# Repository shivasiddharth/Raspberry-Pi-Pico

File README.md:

# Raspberry-Pi-Pico
 Aggregate of Raspberry Pi Pico related codes, firmware, libraries, etc.      

*************************************
## Getting started with Micropython    
*************************************   

### Setting the firmware    
1. Download the MicroPython firmware from the **Firmware** directory in the **Micropython** folder or from official Raspberry Pi's site by clicking [here](https://www.raspberrypi.org/documentation/pico/getting-started/static/5d8e777377e8dbe23cf36360d6efc727/pico_micropython_20210121.uf2).     
2. Push and hold the BOOTSEL button and plug your Pico into the USB port of your Raspberry Pi or other computer. Release the BOOTSEL button after your Pico is detected.     
3. It will mount as a Mass Storage Device called RPI-RP2.     
4. Place the MicroPython UF2 file onto the RPI-RP2 volume. The Raspberry Pi Pico should reboot and be ready for programming using Micropython.   

### Programming the Pico   
1. You can use any Micropython based IDE for programming the Pico. However, the recommended IDE is the Thonny.     
2. Raspberry Pi boards come with Thonny preinstalled. If you are using other systems, you can download and install Thonny from [here](https://thonny.org).    
3. To program the Pico, after opening the Thonny IDE, click on **Run** menu and click on the **Select interpreter** option. And from the Drop-down, select Raspberry Pi Pico.    

**************************************
## Getting started with Circuitpython     
**************************************    

### Setting the firmware
1. Download the MicroPython firmware from the **Firmware** directory in the **Circuitpython** folder or from official Adafruit's site by clicking [here](https://downloads.circuitpython.org/bin/raspberry_pi_pico/en_US/adafruit-circuitpython-raspberry_pi_pico-en_US-6.2.0-beta.0.uf2).     
2. Push and hold the BOOTSEL button and plug your Pico into the USB port of your Raspberry Pi or other computer. Release the BOOTSEL button after your Pico is detected.     
3. It will mount as a Mass Storage Device called RPI-RP2.     
4. Place the Circuitpython UF2 file onto the RPI-RP2 volume. The Raspberry Pi Pico should reboot and ready for programming using Micropython.   

### Programming the Pico   
1. You can use any Circuitpython based IDE for programming the Pico. However, the recommended IDE is the Mu.     
2. Raspberry Pi boards come with Thonny preinstalled. If you are using other systems, you can download and install Mu from [here](https://codewith.mu).    
3. To program the Pico, after opening the Mu IDE. Click on the Serial menu to automatically connect your Pico to the Mu IDE.   
4. Download the desired files from the **Libraries** folder and place it under the **lib** folder on the Pico or download the library zip file and extract it to the **lib** folder on the Pico.   

## Credits to      
1. Adafruit for the Circuitpython libraries and firmware.  
2. Raspberry Pi Foundation for the firmware.   
3. [Peter Hinch](https://github.com/peterhinch) for [micropython-async](https://github.com/peterhinch/micropython-async) and aswitch.py.         
4. [Mike Causer](https://github.com/mcauser) for EEPROM library [micropython-tinyrtc-i2c](https://github.com/mcauser/micropython-tinyrtc-i2c).

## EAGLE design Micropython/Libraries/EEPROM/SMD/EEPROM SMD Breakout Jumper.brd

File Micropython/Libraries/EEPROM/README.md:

## EEPROM Pinout and Connection    
    
The EEPROM has 8 pins, of which 3 are address pins as shown in the figure. The communication between the EEPROm and the microcontroller is via I2C. By setting the address pins A0, A1, A2 to either high or low, the default I2C address of the EEPROM chip can be configured. It is suggested to connect all the address pins to ground, unless you have multiple I2C devices or multiple EEPROMs connected.   

The WP or Write Protect pin when set to high prevents anything from being written on to the EEPROM. When the WP pin is connected to ground, write protection is disabled and things can be written on to the EEPROM.   

And then there is is the usual SDA (I2C Data), SCL (I2C Clock), Vcc (Supply) and Gnd (Ground) pins.    

The SDA, SCL and WP should not be left floating and hence they need to be pulled up via 3.9k resistors. The schematic for the EEPROM has also been attached. Please go through the same for clarity.   

## EEPROM PCB    
I have designed PCBs for making the Pi Pico-EEPROM connection easier. There are variants to the PCB designed. In the sample PCB image, you can see that one has a jumper for write protection and in the other, the write protection pin has been exposed.    

The advantage of using the board with the write protection pin exposed is that, the write protection can be software controlled, i.e., it can be enabled or disabled by setting the pin to Low or High.   

Other than the SMD versions, I have designed DIP versions as well. You can find the eagle files and gerber files here in the aobe folders.   

I got myself the SMD version of the board with the write protection pin exposed printed. I used the services of https://jlcpcb.com for printing as like all my projects. Feel free to modify the the board layout, schematics for your project and get them printed or make your own board using a general purpose PCB.   

## EEPROM-Pi Pico Connection    
My connection is as follows:    

EEPROM SDA --> Pi Pico GP0    

EEPROM SDA --> Pi Pico GP1    

EEPROM VCC --> Pi Pico 3V3 (OUT)    

EEPROM WP --> Pi Pico GND    

EEPROm GND --> Pi Pico GND    

The Raspberry Pi Pico has a number of I2C lines. Choose the ones comfortable to you.    

## Using the EEPROM in Your Program   
I have used Micropython to work with the EEPROM chip. I have modified the Micropython EERPOM libraries of [Mike Causer](https://github.com/mcauser).      

There are two parameters of the EEPROM to consider which are the bytes per page(bpp or BPP) and the pages. The total EEPROM memory is BPP x Number of Pages.    

For the same EEPROM capacity different manufactures may have different values of BPP and Number of Pages. Make sure to check them out and change those values in the library files.    

I have provided library files for two different versions just for reference and to show the difference. If you are using any other EEPROM version please do pay attention to the shown differences and change your library file accordingly.    

After making the desired changes to the library file, import it onto the Pi Pico. I have provided a demo script that exploits almost all the functions of the EEPROM. You cna find the demo script in the examples folder.   

I have gone through a lot of detail and have explained the demo script in this video below.

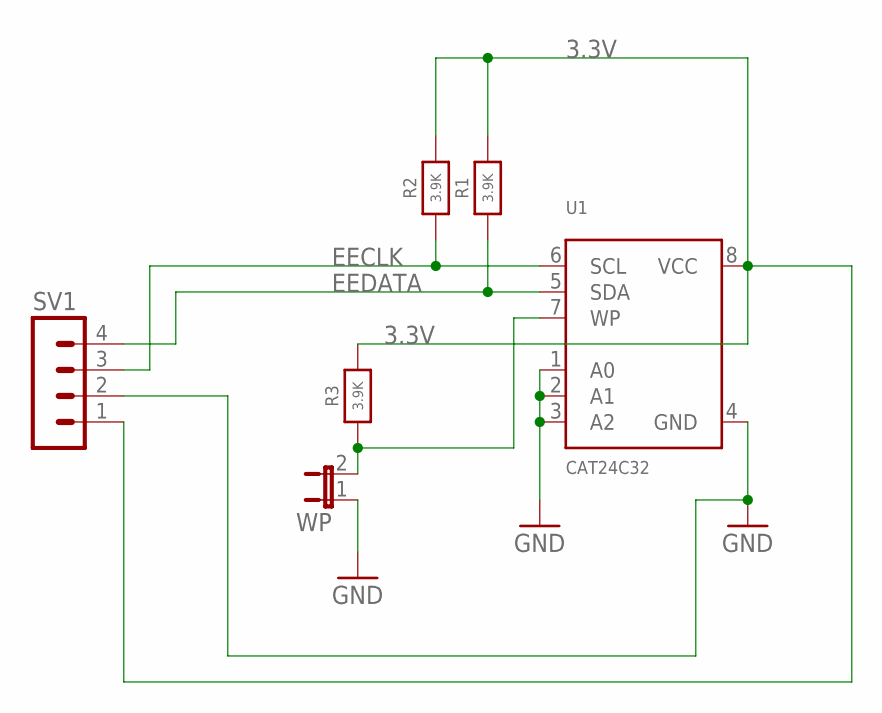
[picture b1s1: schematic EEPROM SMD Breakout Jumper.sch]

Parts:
R1, R2, R3: 3.9K; 0805-NO
SV1: MA04-1
U1: CAT24C32; SOIC8_150MIL
WP: JP1E; JP1

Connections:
3.3V: R1.2, R2.2, R3.2, SV1.1, U1.8 (VCC)
EECLK: R2.1, SV1.3, U1.6 (SCL)
EEDATA: R1.1, SV1.4, U1.5 (SDA)
GND: SV1.2, U1.1 (A0), U1.2 (A1), U1.3 (A2), U1.4 (GND), WP.1
unnamed: R3.1, U1.7 (WP), WP.2

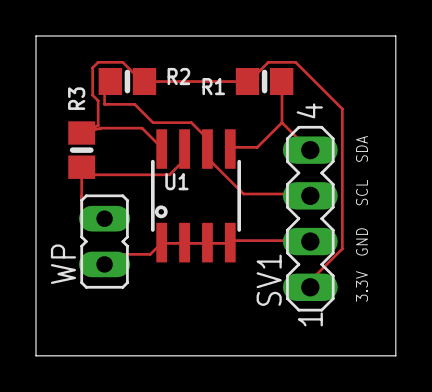
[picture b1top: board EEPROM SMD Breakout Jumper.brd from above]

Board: 2 copper layers, 20.0 x 17.8 mm, 6 parts (0 on the bottom side), 5 nets.

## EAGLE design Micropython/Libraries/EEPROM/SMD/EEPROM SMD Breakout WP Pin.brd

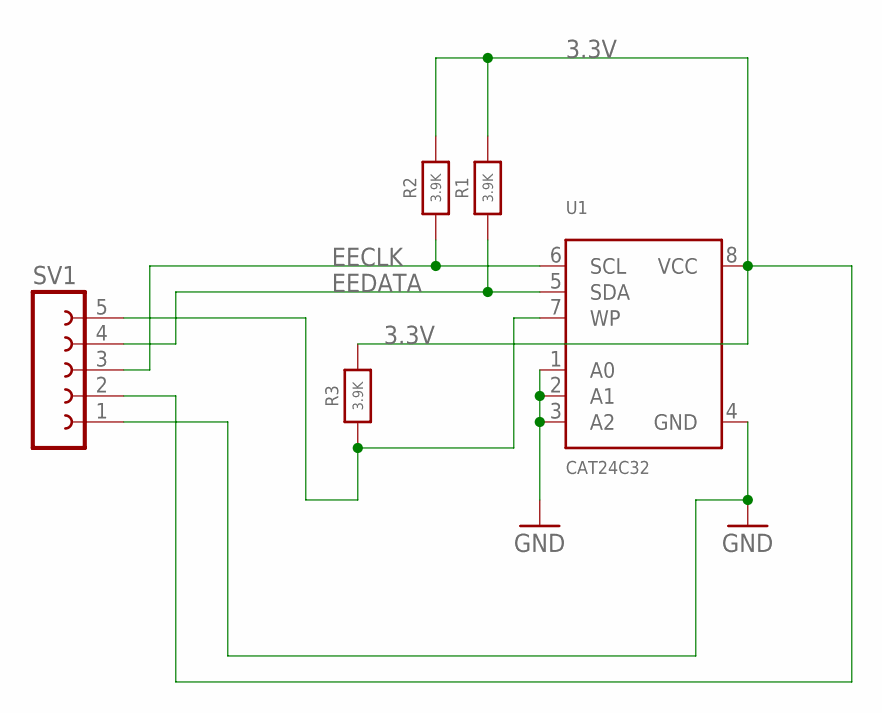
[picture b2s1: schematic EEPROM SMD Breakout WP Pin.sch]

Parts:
R1, R2, R3: 3.9K; 0805-NO
SV1: FE05-1
U1: CAT24C32; SOIC8_150MIL

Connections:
3.3V: R1.2, R2.2, R3.2, SV1.2, U1.8 (VCC)
EECLK: R2.1, SV1.3, U1.6 (SCL)
EEDATA: R1.1, SV1.4, U1.5 (SDA)
GND: SV1.1, U1.1 (A0), U1.2 (A1), U1.3 (A2), U1.4 (GND)
unnamed: R3.1, SV1.5, U1.7 (WP)

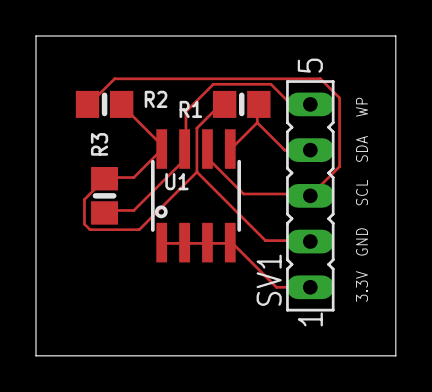
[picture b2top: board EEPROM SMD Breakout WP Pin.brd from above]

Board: 2 copper layers, 20.0 x 17.8 mm, 5 parts (0 on the bottom side), 5 nets.

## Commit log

2021-01-26 Publish the Git
    Publishing the git
2021-01-26 Update README.md
    Add README image
2021-01-26 Added Circuitpython libraries
2021-01-26 Add circuitpython examples
2021-01-26 Update Circuitpython examples
2021-01-27 Rename blink-timer-set.py to blink-timer-one-shot.py
2021-01-27 Rename blink-timer-one-shot.py to blink-timer-fixed-times.py
2021-01-28 Add timer example
    Added a seperate folder for timer samples.
2021-02-08 Added pushbutton examples
2021-02-22 Add EEPROM
    Added sample, library,circuit and board files.

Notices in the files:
parts and their libraries:
microbuilder: This work is placed in the public domain, and may be freely used for commercial and non-commercial work with the following conditions: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
